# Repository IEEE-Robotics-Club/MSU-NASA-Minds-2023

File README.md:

# MSU-NASA-Minds-2023
The code repository for the 2023 MSU NASA Minds competition. This year we will explore different cooperative imformation gathering techniques via simulation and building a homogenous robotic swarm. This repository will be split up into several different sections:

## ARGoS Robotic Swarm Simulator: 

We will be modelling and testing our system methods using ARGoS Robotic Simulator. This will serve the purpose of testing our movement algorithms and swarm logic.  

### Getting Started with ARGoS Simulator on an Ubuntu Machine:

1. Install ARGoS as per directions here https://www.argos-sim.info/core.php 

2. Clone the ARGoS-Simulations Repository and save it in a memorable place. 

3. Navigate to the repository using the terminal and run the command:

  `$ argos3 -c  Tellus-Prototype/tellus.argos

This will run the example simulation and also open the Lua editor where you can change the Robot's behaviour with a Lua Script.

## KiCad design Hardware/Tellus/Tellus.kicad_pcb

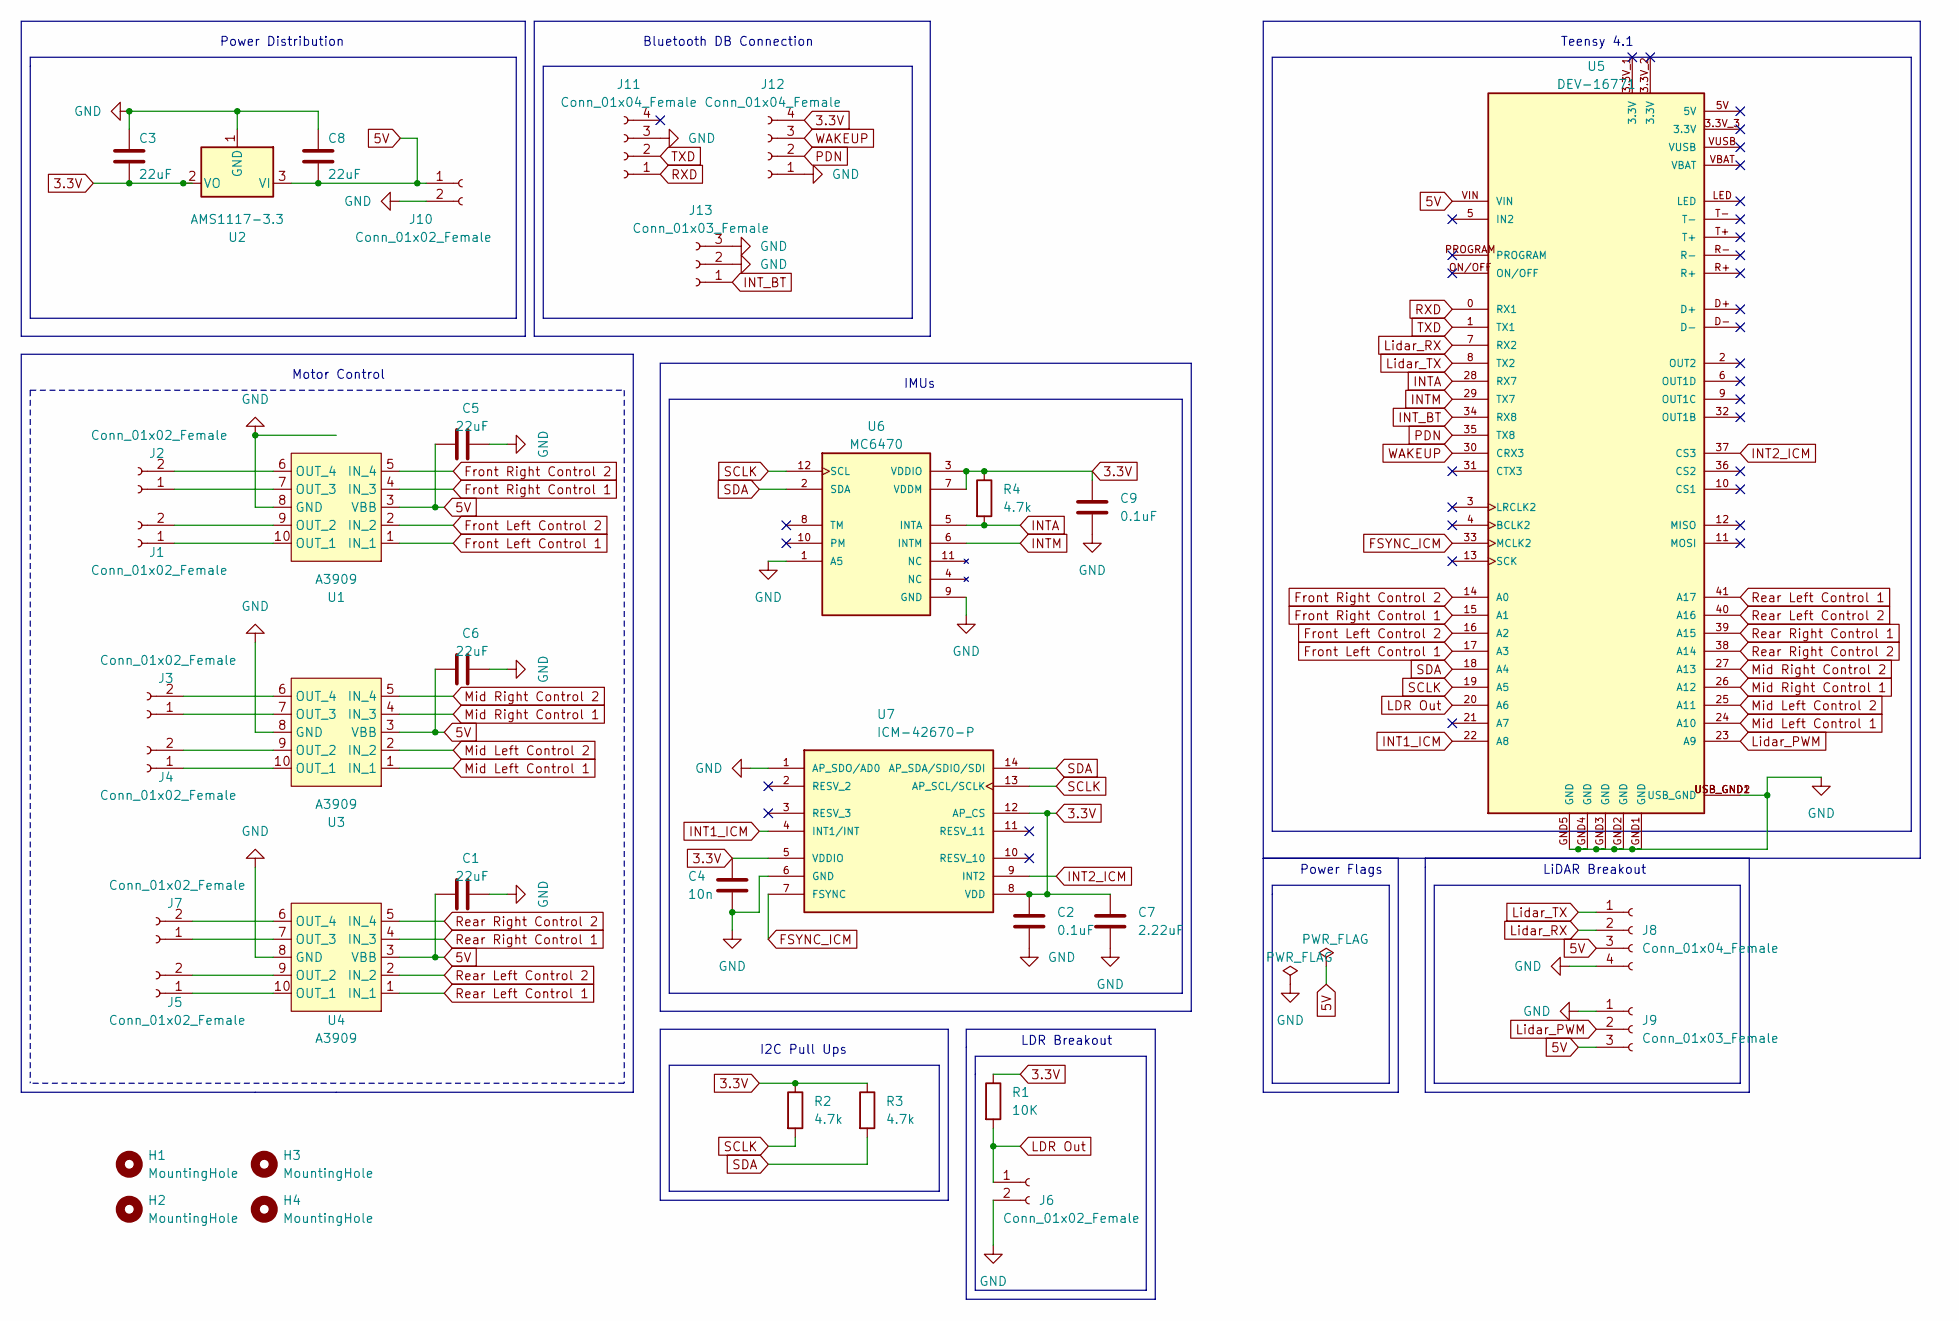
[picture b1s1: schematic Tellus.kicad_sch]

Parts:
C1, C3, C5, C6, C8: 22uF; C_1210_3225Metric_Pad1.33x2.70mm_HandSolder
C2, C9: 0.1uF; C_1210_3225Metric_Pad1.33x2.70mm_HandSolder
C4: 10n; C_1210_3225Metric_Pad1.33x2.70mm_HandSolder
C7: 2.22uF; C_1210_3225Metric_Pad1.33x2.70mm_HandSolder
H1, H2, H3, H4: MountingHole
J1, J2, J3, J4, J5, J6, J7, J10: Conn_01x02_Female; PinHeader_1x02_P2.54mm_Vertical
J8: Conn_01x04_Female; PinHeader_1x04_P2.54mm_Vertical
J9: Conn_01x03_Female; PinHeader_1x03_P2.54mm_Vertical
J11, J12: Conn_01x04_Female; PinHeader_1x04_P2.00mm_Vertical
J13: Conn_01x03_Female; PinHeader_1x03_P2.00mm_Vertical
R1: 10K; R_1206_3216Metric
R2, R3, R4: 4.7k; R_1206_3216Metric
U1, U3, U4: A3909; SSOP-10_3.9x4.9mm_P1.00mm
U2: AMS1117-3.3; SOT-89-3
U5: DEV-16771; MODULE_DEV-16771; PARTREV 4.1
U6: MC6470; PQFN50P200X200X100-12N; PARTREV 1.7
U7: ICM-42670-P; IC_ICM-42670-P

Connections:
3.3V: C2.1, C3.2, C4.1, C7.1, C9.1, J12.4, R1.1, R2.1, R3.1, R4.1, U2.2 (VO), U6.3 (VDDIO), U6.7 (VDDM), U7.5 (VDDIO), U7.8 (VDD), U7.12 (AP_CS)
5V: C1.1, C5.1, C6.1, C8.2, J8.3, J9.3, J10.1, U1.3 (VBB), U2.3 (VI), U3.3 (VBB), U4.3 (VBB), U5.VIN
FSYNC_ICM: U5.33 (MCLK2), U7.7 (FSYNC)
Front Left Control 1: U1.1 (IN_1), U5.17 (A3)
Front Left Control 2: U1.2 (IN_2), U5.16 (A2)
Front Right Control 1: U1.4 (IN_3), U5.15 (A1)
Front Right Control 2: U1.5 (IN_4), U5.14 (A0)
GND: C1.2, C2.2, C3.1, C4.2, C5.2, C6.2, C7.2, C8.1, C9.2, J6.2, J8.4, J9.1, J10.2, J11.3, J12.1, J13.2, J13.3, U1.8 (GND), U2.1 (GND), U3.8 (GND), U4.8 (GND), U5.GND1 (GND), U5.GND2 (GND), U5.GND3 (GND), U5.GND4 (GND), U5.GND5 (GND), U5.USB_GND1 (USB_GND), U5.USB_GND2 (USB_GND), U6.1 (A5), U6.9 (GND), U7.1 (AP_SDO/AD0), U7.6 (GND)
INT1_ICM: U5.22 (A8), U7.4 (INT1/INT)
INT2_ICM: U5.37 (CS3), U7.9 (INT2)
INTA: R4.2, U5.28 (RX7), U6.5 (INTA)
INTM: U5.29 (TX7), U6.6 (INTM)
INT_BT: J13.1, U5.34 (RX8)
LDR Out: J6.1, R1.2, U5.20 (A6)
Lidar_PWM: J9.2, U5.23 (A9)
Lidar_RX: J8.2, U5.7 (RX2)
Lidar_TX: J8.1, U5.8 (TX2)
Mid Left Control 1: U3.1 (IN_1), U5.24 (A10)
Mid Left Control 2: U3.2 (IN_2), U5.25 (A11)
Mid Right Control 1: U3.4 (IN_3), U5.26 (A12)
Mid Right Control 2: U3.5 (IN_4), U5.27 (A13)
unnamed: J1.1, U1.10 (OUT_1)
unnamed: J1.2, U1.9 (OUT_2)
unnamed: J2.1, U1.7 (OUT_3)
unnamed: J2.2, U1.6 (OUT_4)
unnamed: J3.1, U3.7 (OUT_3)
unnamed: J3.2, U3.6 (OUT_4)
unnamed: J4.1, U3.10 (OUT_1)
unnamed: J4.2, U3.9 (OUT_2)
unnamed: J5.1, U4.10 (OUT_1)
unnamed: J5.2, U4.9 (OUT_2)
unnamed: J7.1, U4.7 (OUT_3)
unnamed: J7.2, U4.6 (OUT_4)
PDN: J12.2, U5.35 (TX8)
RXD: J11.1, U5.0 (RX1)
Rear Left Control 1: U4.1 (IN_1), U5.41 (A17)
Rear Left Control 2: U4.2 (IN_2), U5.40 (A16)
Rear Right Control 1: U4.4 (IN_3), U5.39 (A15)
Rear Right Control 2: U4.5 (IN_4), U5.38 (A14)
SCLK: R2.2, U5.19 (A5), U6.12 (SCL), U7.13 (AP_SCL/SCLK)
SDA: R3.2, U5.18 (A4), U6.2 (SDA), U7.14 (AP_SDA/SDIO/SDI)
TXD: J11.2, U5.1 (TX1)
WAKEUP: J12.3, U5.30 (CRX3)

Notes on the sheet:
I2C Pull Ups
LiDAR Breakout
LDR Breakout
Motor Control
Power Distribution
IMUs
Teensy 4.1
Power Flags
Bluetooth DB Connection

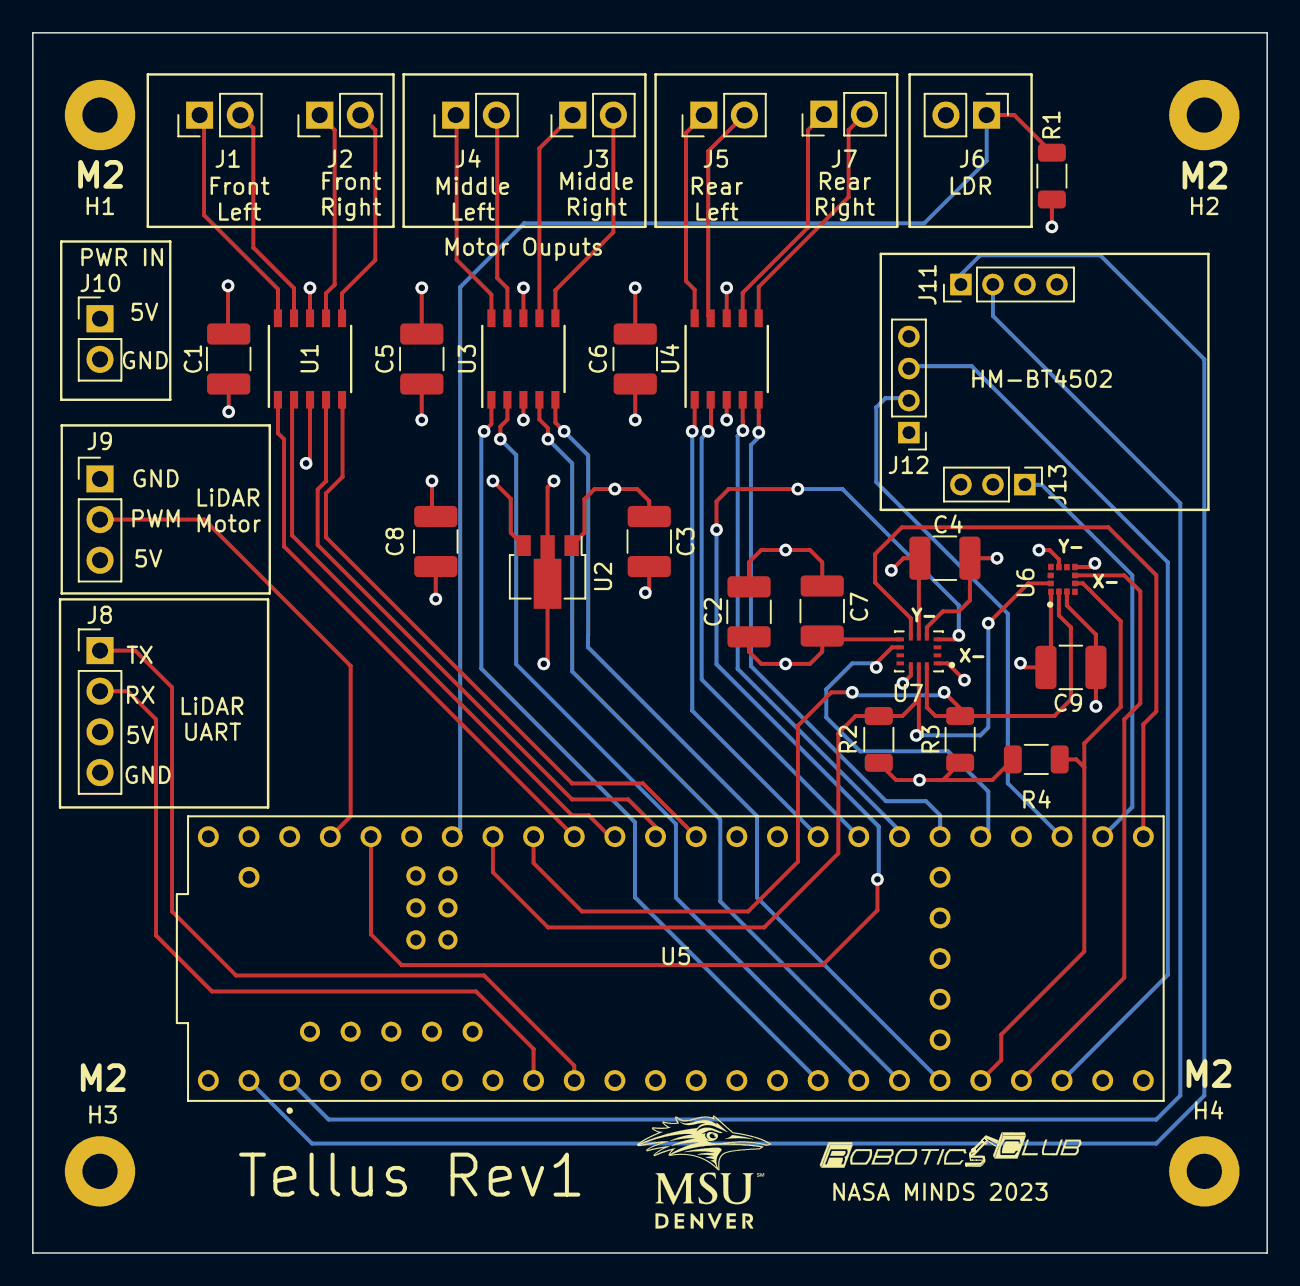
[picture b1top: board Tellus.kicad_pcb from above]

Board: 4 copper layers, 77.1 x 76.2 mm, 37 parts (0 on the bottom side), 43 nets.

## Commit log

2022-09-15 Rename docs/README.md to Docs/README.md
2022-09-15 Create template motors.h
    Once we get going on the motors, we'll place their function signatures here
2022-09-15 Update motor-API's README.md with clarification
2022-09-19 Add embedded systems diagram
2022-09-23 Added structure API for basic motor interfacing
2022-10-05 Added protocol flowchart iteration 1
2022-10-09 Vector library & hpp extensions
    Added my vector library code from previous year's robotics competition. Not likely to change much over the course of the project. Removed .c file for motor control since we don't have an implementati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
2022-10-12 Improved documentation for vector functions
2022-10-12 modified motor func to use updated header ext.
2022-10-12 changed i, j, k to x, y, z in vector functions
2022-10-12 Obstacle Avoidance Flowchart
    with love - tyler
2022-10-12 Obstance Avoidance
    with love - tyler
2022-10-13 Create movement protocol chart
    Created the movement control sub-protocol chart
2022-10-13 Removed extraneous motor function signatures
2022-10-13 Moved movement control to docs
2022-10-13 Change type name & add servo func signatures
    I changed motor to motor_t, and added some basic templates for pwm and servo control
2022-10-18 Moved code into codebase folder
2022-10-19 Relocated charts from Hardware to Docs
2022-10-19 removed duplicate files
2022-10-22 Added geometry submodule
2022-10-26 Fixed lua imports for the prototype example
2022-10-26 Removed Excess Experiments from Repo
2022-10-26 More Cleanup
2022-10-26 Shopping list for electrical
    >:)
2022-10-26 Add Embedded systems Bill of Materials
2022-10-26 Add microcontroller comparison doc
2022-11-04 Communication Protocol Flowcharts
    Sending and receiving messages
2022-11-04 Add files via upload
    Sending and receiving messages
2022-11-04 Merge recieve & send comms protocols
    Sending and receiving messages
2022-11-16 Delete Electrical Block Diagram.png
    OLD FILE
2022-11-16 Add files via upload
    NEW FILE
2022-11-16 Delete Electrical Block Diagram.png (#19)
    OLD FILE
2022-11-16 Add files via upload (#20)
    NEW FILE
2022-11-16 added final result for now as of 11/16 4:39
2022-11-16 tyleerr
2022-11-17 miles
2022-11-17 we dont need this gosh darn function anymore, i literally h*te this function so much >:(
2022-11-17 Merge tyler (#23)
    * added final result for now as of 11/16 4:39
    * tyleerr
    * we dont need this gosh darn function anymore, i literally h*te this function so much >:(
2022-11-17 Update Movement control sub-protocol to mention LIDAR
2022-11-17 ELECTRICAL PLAN FOR NEXT MEETING
2022-11-30 create memory pool outline
2022-12-01 update gitignore to include .vscode folder
2022-12-01 new argos project for prototyping
2022-12-01 add image assets
2022-12-01 create preliminary motor wrappers to mirror final robot code & aid in code translatability between platforms
2022-12-01 Add a speed factor for pwm values
2022-12-01 Added Controller definitions for Battery, Radios, Ground Sensor, Positioning, and Proximity sensors.
2022-12-01 typo fix
2022-12-05 add lua state machine submodule
2022-12-05 configure vscode properties to better recognize C
2022-12-05 move location of MoonSurface.png
2022-12-05 add lua motor function wrapper outlines
2022-12-12 Replace pwm with speed & fix motor_drive
2022-12-12 alter lua-state-machine submodule
2023-01-01 Finished Tellus ARGoS Prototype
2023-01-02 Added Lidar encoder and middle wheel control
2023-01-11 Added Tellus Motherboard Rev1
2023-01-25 Push local changes for now
2023-01-27 root commit
2023-01-27 add lsm submodule
2023-01-27 create gitignore
2023-01-27 copy lsm file for simplicity
2023-01-27 basic callback test
2023-01-27 Update LSM
2023-01-27 remove lsm submodule
2023-01-30 add statemachine.lua to root dir
2023-01-30 (sm) add outline of movement control protocol
2023-01-30 Update missing info in README
2023-02-01 removed extraneous file
2023-02-02 Revert "removed extraneous file"
    This reverts commit 8dd7fa58d26d70743817fa4eb39adb717178ac78.
2023-02-02 updated simulation texture path
2023-02-02 add statemachine
2023-02-02 outline waypoints functionality
2023-02-02 add pathfind file
2023-02-02 outline pathfinding/driving state machine
2023-02-02 Added Middle wheel control
2023-02-03 added middle wheels to movement functions
2023-02-03 test: swapped middle wheels in driveForward
2023-02-05 PCB Updates
    Re-Layered PCB to match Signal, PWR, GND, Signal suggestion. Cleaned up power connections, Bluetooth saddle, and LiDAR mounts.
    Fixed the following DRC Violations/Warnings:
    No Footprint assigned for Mounting holes
    - Fixed by adding them in the schematic.
    Unconnected 3.3V Terminals on Teensy
    - Fixed Symbol in schematic that had them on top of each other. The teensy spec does not recommend tying these together.
2023-02-05 Added Logos
    Added MSU Logo and Robotics Club Logo to the front and back silkscreen layers
2023-02-05 Cleanup
2023-02-07 add utility functions
2023-02-07 Final Edits and Manufacturer File Generation
2023-02-07 Started Lidar Mapping Library
2023-02-08 unfinished map implementation
2023-02-08 Merge robot config file additions from main to pathfinding_test (#30)
    * Added Middle wheel control
    * Add files via upload
    * Add files via upload
    * Add files via upload
    * Add files via upload
    * Add files via upload
2023-02-08 add movement-functions to tellus directory
2023-02-08 fixed middle wheel rotation for each movement function
2023-02-09 Fixed Movement Functions and created a drive test experiment file
2023-02-09 Modified the drive test experiment file
    Added comments to coop scan
2023-02-09 Restructured the project and lidar features
2023-02-10 Restructured the project and lidar features (#38)
2023-02-16 Started the point map data structure
    Also changed the lidar readings to be in radians instead of degrees
2023-03-01 Revisions to the lidar experiments
2023-03-01 Fixed issues with lidar setup
    Fixed problems with lidar setup including using radians instead of degrees for the {angle, distance} table.
    Also removed tellus-lidar.argos and replaced it with lidar-test.argos
2023-03-10 added first pass on Motor and Motion classes
2023-03-11 Added Arduino Libraries for the IMUs
    Ported the MC7XXX Over to C++ and added with Wire interface to work with Arduino.
2023-03-24 Added checkerboard scan with tellus
2023-03-25 Dummy Thicc commit
2023-03-25 and i oop
2023-03-25 summary (requred)
2023-03-25 bugs bunny
2023-03-25 x/y fix
2023-03-26 Added old model version of checkerboard
2023-03-29 Checkerboard Matlab
2023-03-29 Added offset and started metrics
2023-03-29 Added Coverage display
2023-03-29 added radius field to initialization
